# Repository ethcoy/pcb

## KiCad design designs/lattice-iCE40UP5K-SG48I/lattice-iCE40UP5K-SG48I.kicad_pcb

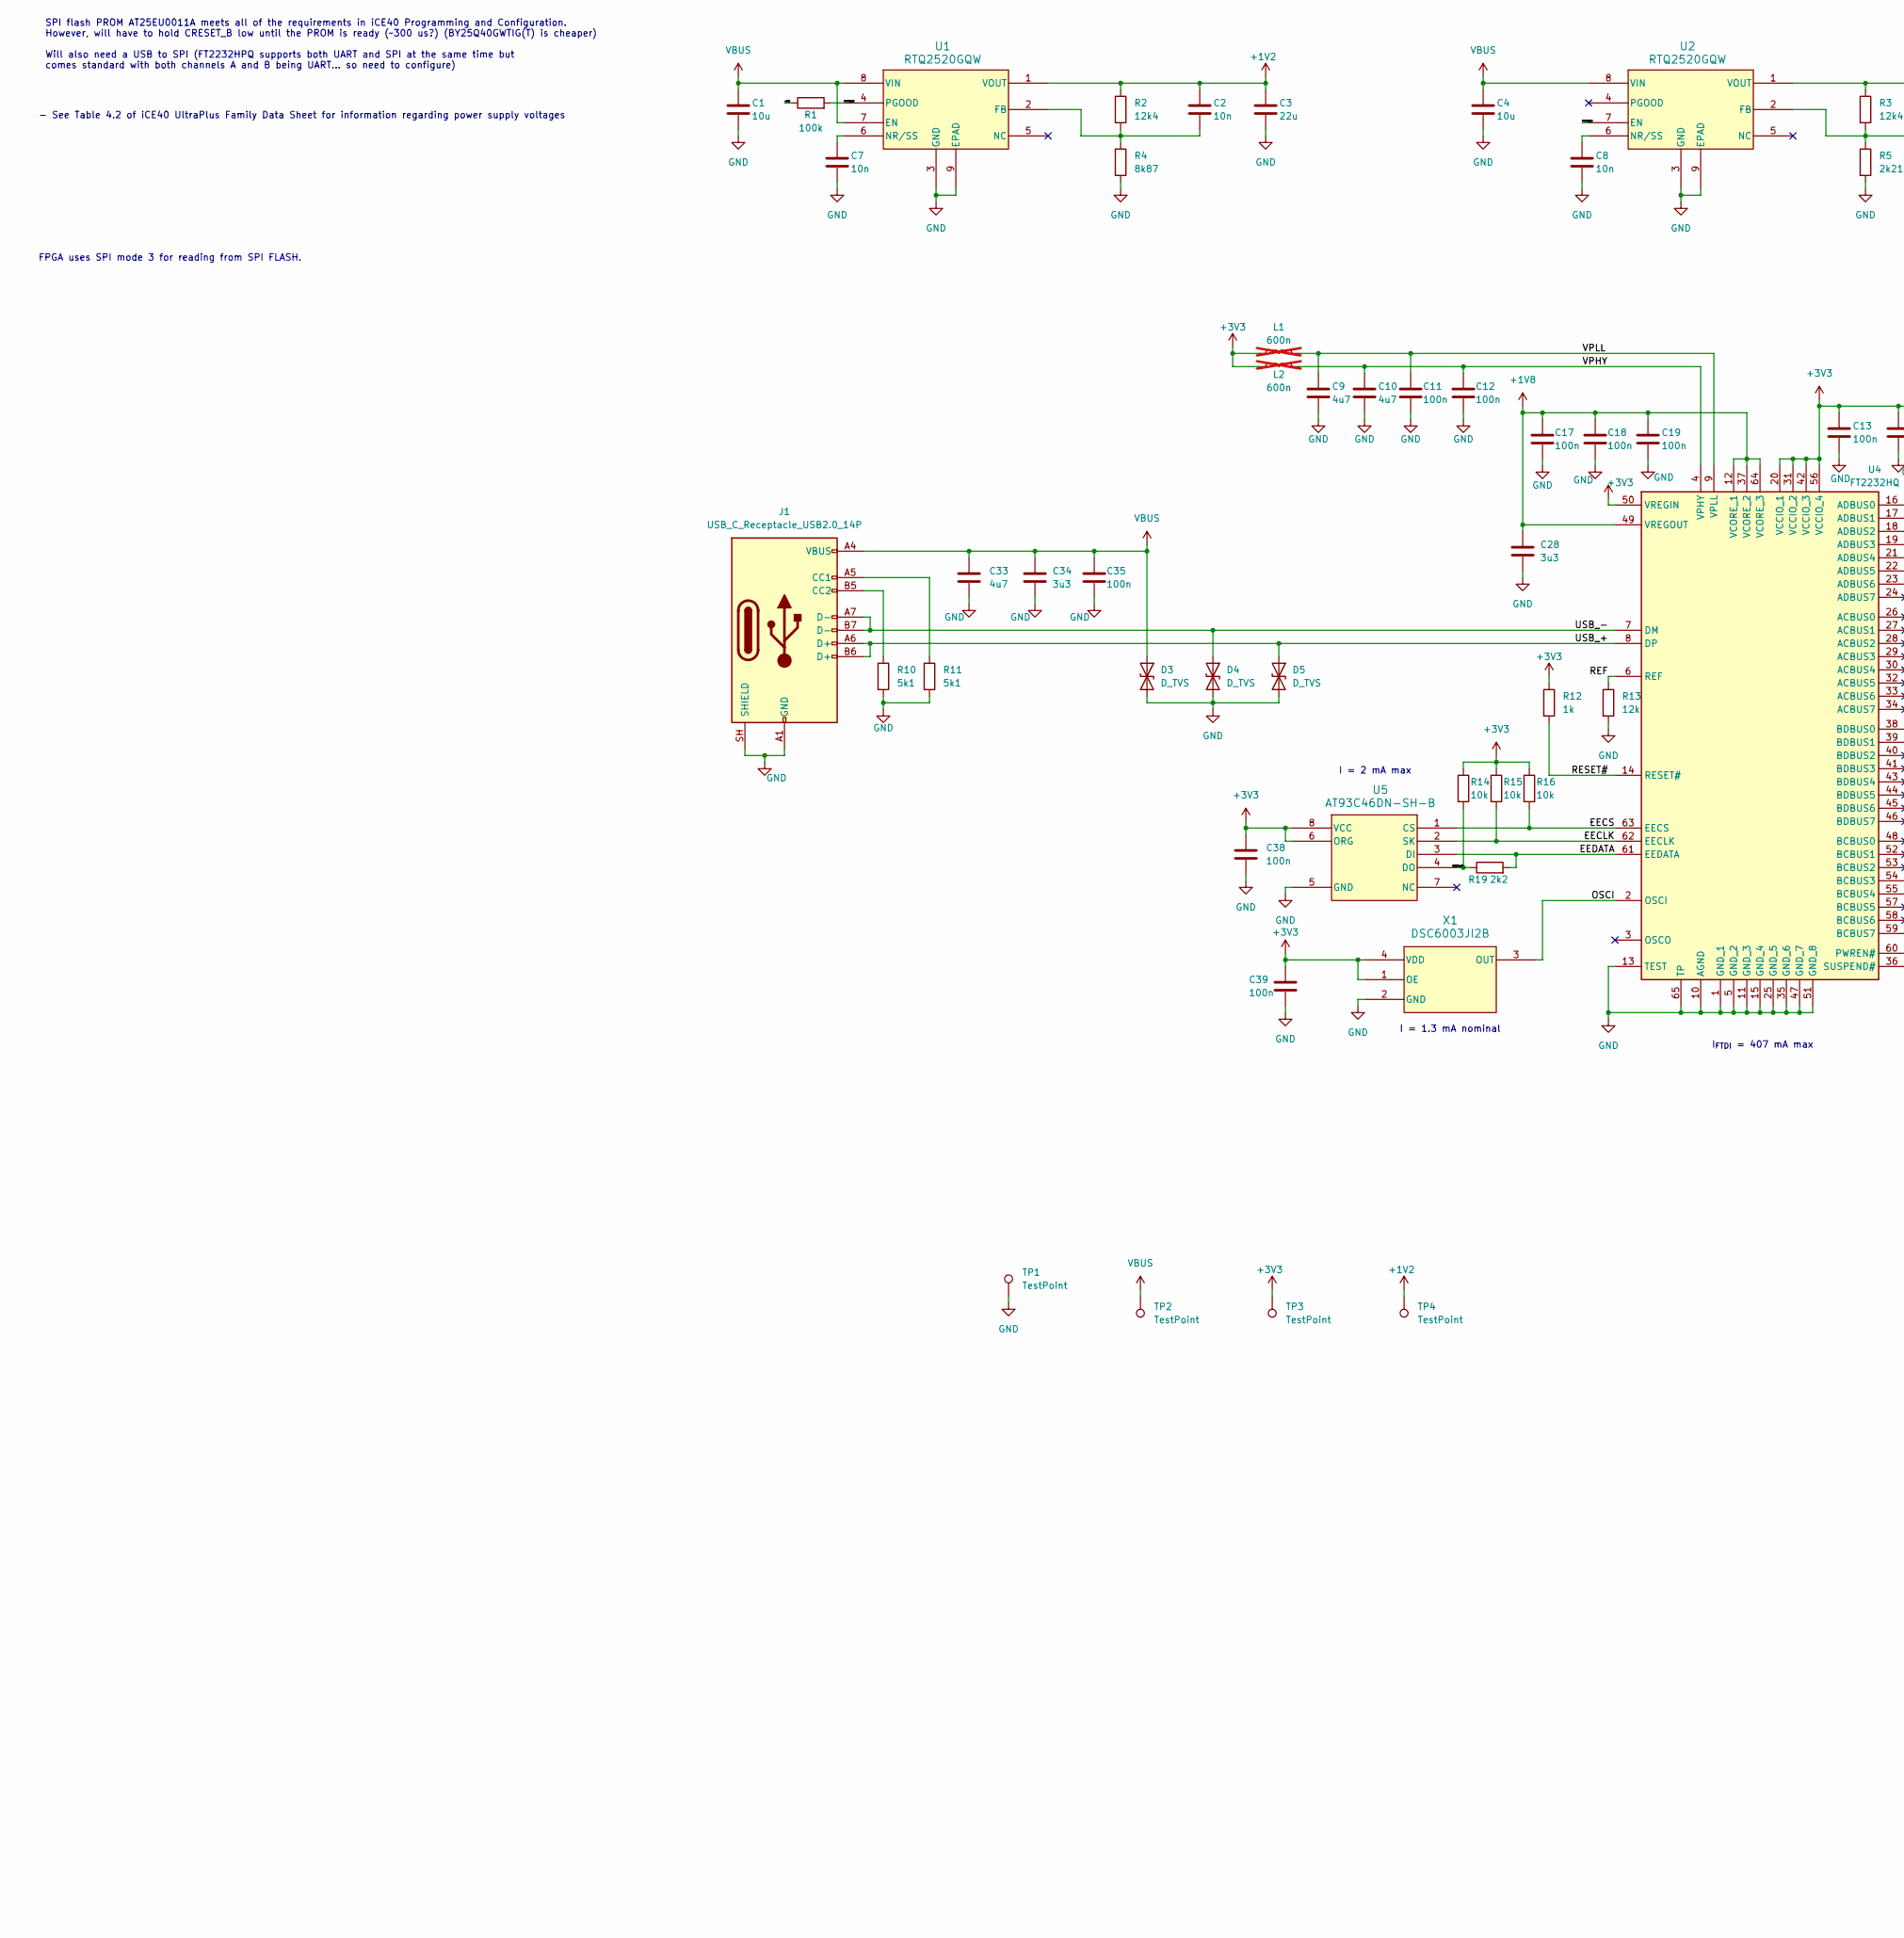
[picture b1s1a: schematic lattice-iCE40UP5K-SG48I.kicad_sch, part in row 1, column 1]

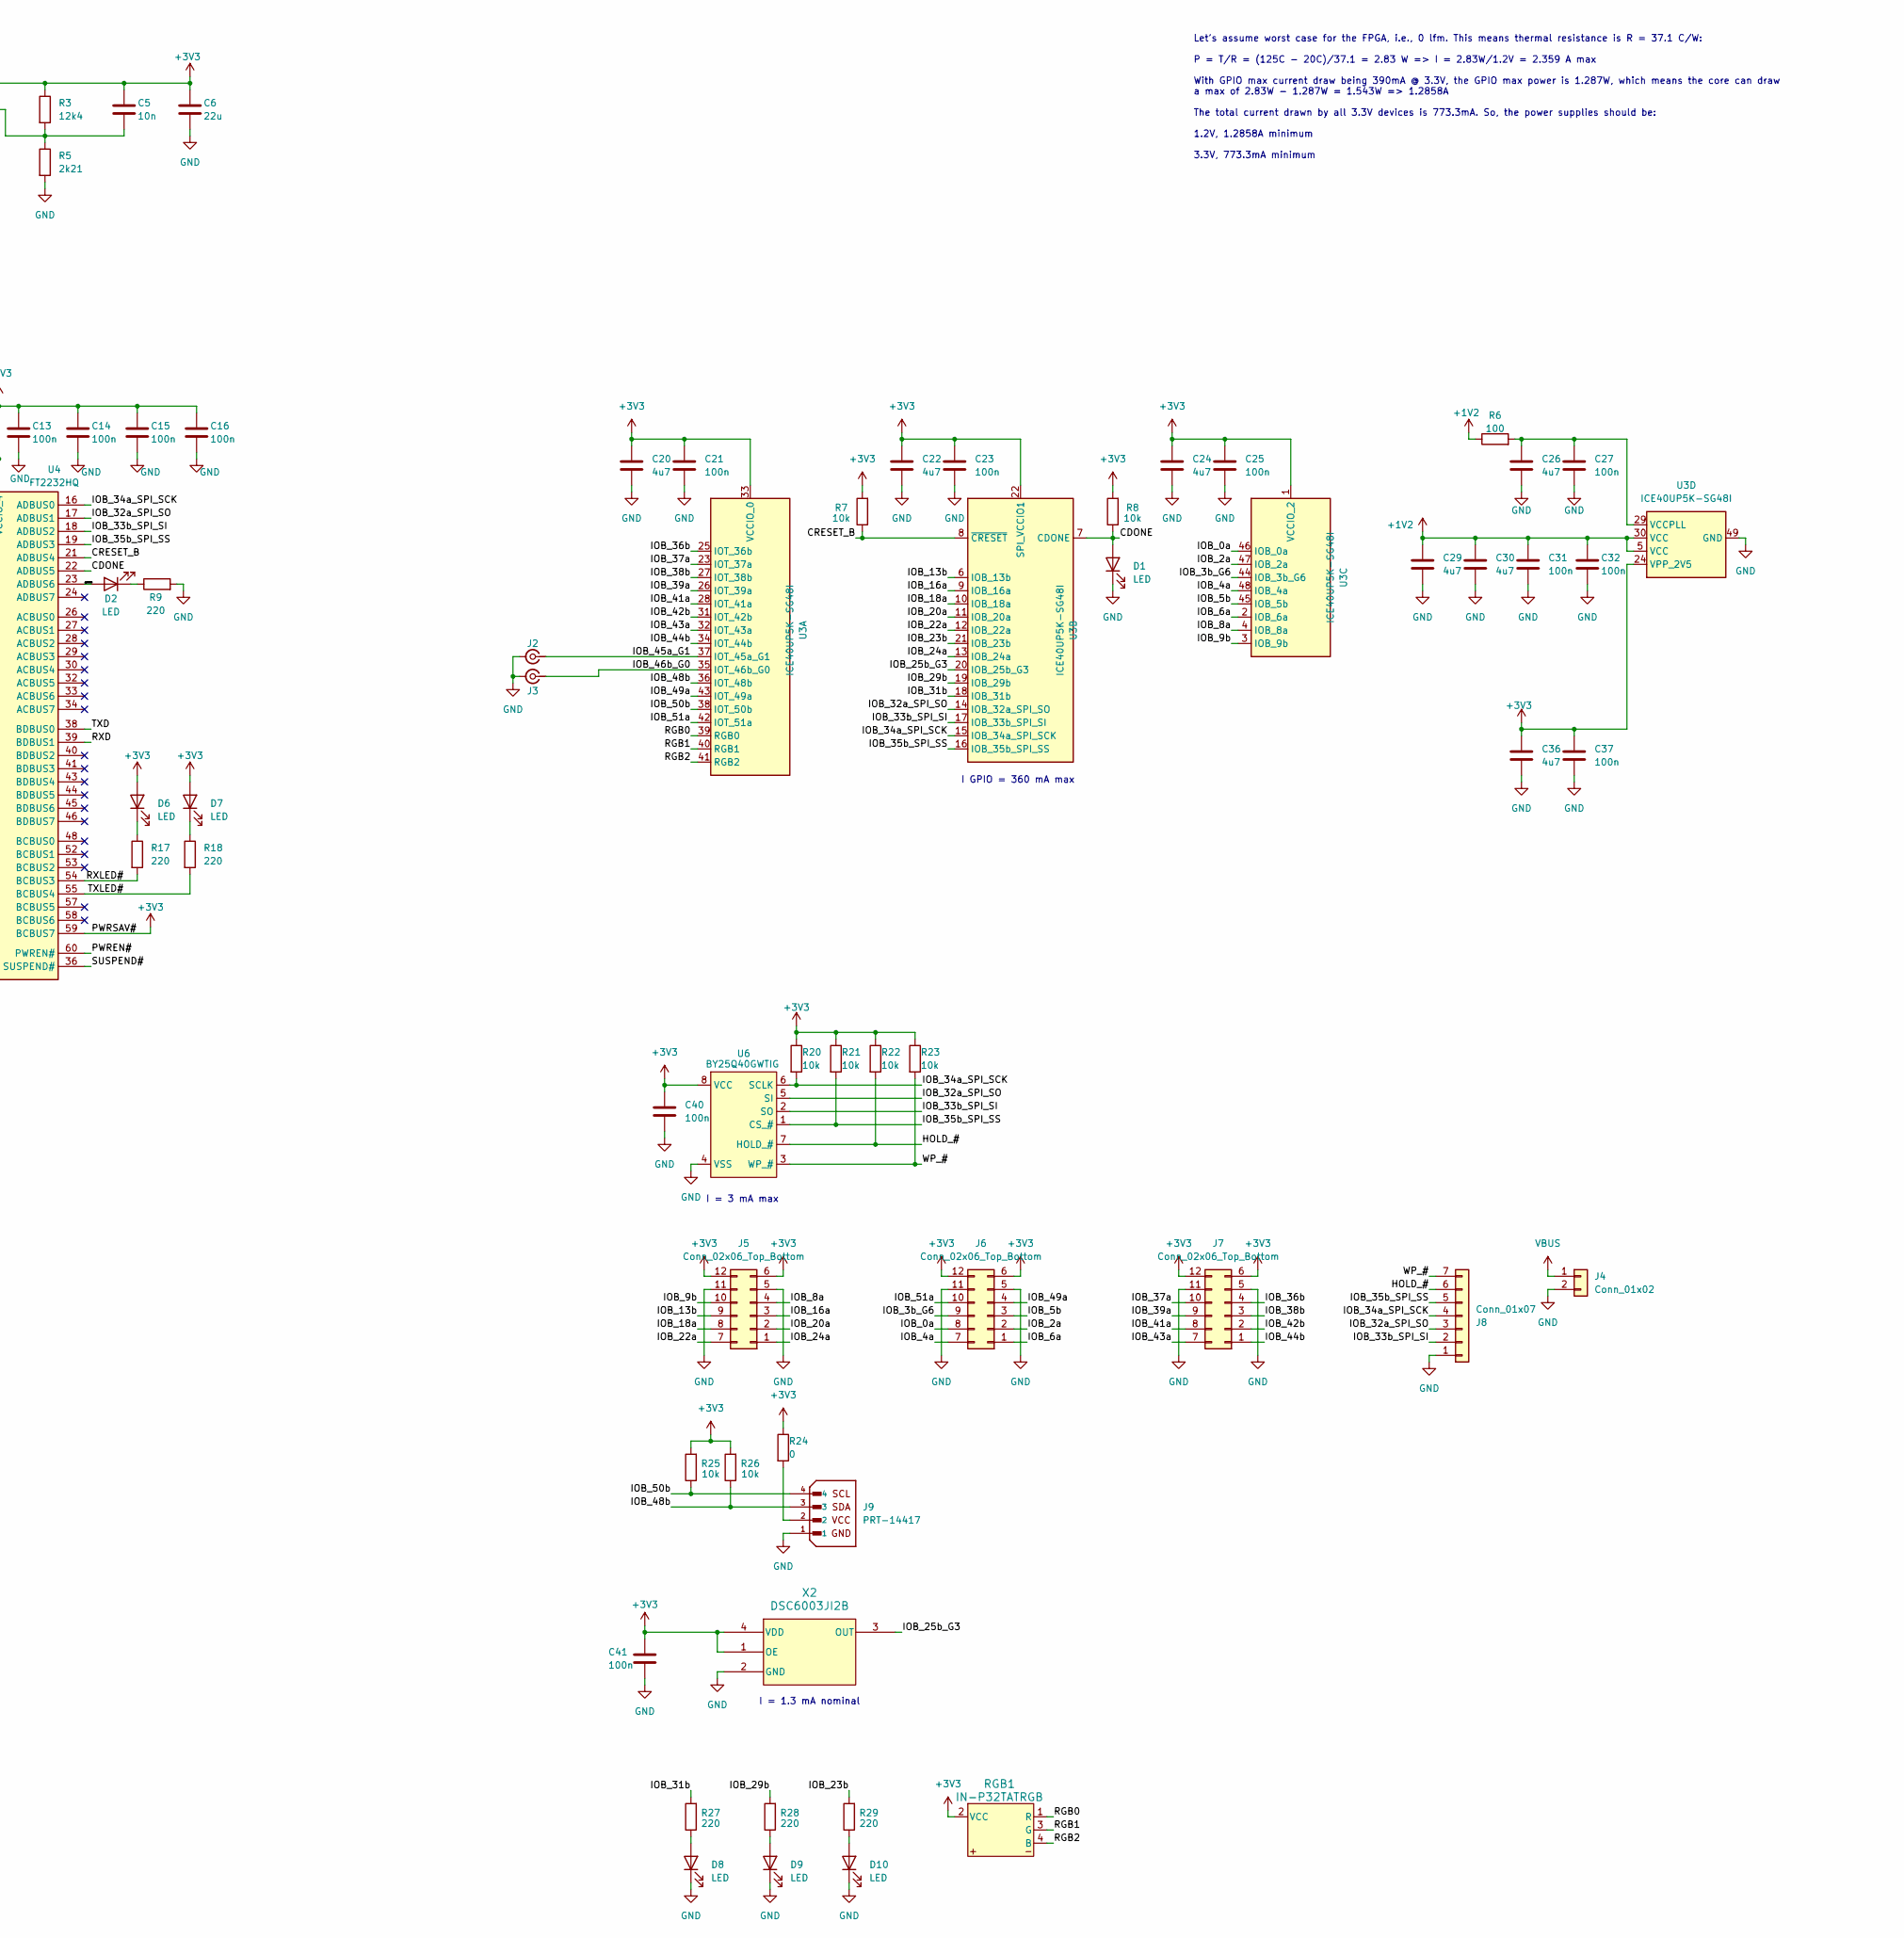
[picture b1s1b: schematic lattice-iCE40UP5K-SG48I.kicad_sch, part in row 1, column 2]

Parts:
C1, C4: 10u; C_0402_1005Metric
C2, C5, C7, C8: 10n; C_0402_1005Metric
C3, C6: 22u; C_0402_1005Metric
C9, C10, C20, C22, C24, C26, C29, C30, C33, C36: 4u7; C_0402_1005Metric
C11, C12, C13, C14, C15, C16, C17, C18, C19, C21, C23, C25, C27, C31, C32, C35, C37, C38, C39, C40, C41: 100n; C_0402_1005Metric
C28, C34: 3u3; C_0402_1005Metric
D1, D2, D6, D7, D8, D9, D10: LED; D_0402_1005Metric
D3, D4, D5: D_TVS; D_SOD-523
J1: USB_C_Receptacle_USB2.0_14P; USB_C_Receptacle_GCT_USB4110
J2: Conn_Coaxial_Small; U.FL_Molex_MCRF_73412-0110_Vertical
J3: U.FL_Molex_MCRF_73412-0110_Vertical
J4: Conn_01x02; PinHeader_1x02_P2.54mm_Vertical_SMD_Pin1Left
J5, J6, J7: Conn_02x06_Top_Bottom; SAMTEC-SMH-106-02-X-D
J8: Conn_01x07; PinHeader_1x07_P2.54mm_Vertical_SMD_Pin1Left
J9: PRT-14417; PARTREV NA
L1, L2: 600n; L_0402_1005Metric; not fitted
R1: 100k; R_0402_1005Metric
R2, R3: 12k4; R_0402_1005Metric
R4: 8k87; R_0402_1005Metric
R5: 2k21; R_0402_1005Metric
R6: 100; R_0402_1005Metric
R7, R8, R14, R15, R16, R20, R21, R22, R23, R25, R26: 10k; R_0402_1005Metric
R9, R17, R18, R27, R28, R29: 220; R_0402_1005Metric
R10, R11: 5k1; R_0402_1005Metric
R12: 1k; R_0402_1005Metric
R13: 12k; R_0402_1005Metric
R19: 2k2; R_0402_1005Metric
R24: 0; R_0402_1005Metric
RGB1: IN-P32TATRGB; 4-PLCC_3P2X2P8_INL
TP1, TP2, TP3, TP4: TestPoint; TestPoint_Pad_D1.0mm
U1, U2: RTQ2520GQW
U3: ICE40UP5K-SG48I; QFN50P700X700X100-49N-D
U4: FT2232HQ; Mouser Part Number 895-FT2232HQ
U5: AT93C46DN-SH-B
U6: BY25Q40GWTIG
X1, X2: DSC6003JI2B

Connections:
+1V2: C2.1, C3.1, C29.1, C30.1, C31.1, C32.1, R1.1, R2.1, R6.1, TP4.1 (1_1), U1.1 (VOUT), U3.5 (VCC), U3.30 (VCC)
+1V8: C17.1, C18.1, C19.1, C28.1, U4.12 (VCORE_1), U4.37 (VCORE_2), U4.49 (VREGOUT), U4.64 (VCORE_3)
+3V3: C5.1, C6.1, C13.1, C14.1, C15.1, C16.1, C20.1, C21.1, C22.1, C23.1, C24.1, C25.1, C36.1, C37.1, C38.1, C39.1, C40.1, C41.1, D6.2 (A), D7.2 (A), J5.6, J5.12, J6.6, J6.12, J7.6, J7.12, L1.1, L2.1, R3.1, R7.2, R8.2, R12.1, R14.1, R15.1, R16.1, R20.1, R21.1, R22.1, R23.1, R24.1, R25.2, R26.2, RGB1.2 (VCC), TP3.1 (1_1), U2.1 (VOUT), U3.1 (VCCIO_2), U3.22 (SPI_VCCIO1), U3.24 (VPP_2V5), U3.33 (VCCIO_0), U4.20 (VCCIO_1), U4.31 (VCCIO_2), U4.42 (VCCIO_3), U4.50 (VREGIN), U4.56 (VCCIO_4), U4.59 (BCBUS7), U5.6 (ORG), U5.8 (VCC), U6.8 (VCC), X1.1 (OE), X1.4 (VDD), X2.1 (OE), X2.4 (VDD)
/ADBUS6: D2.2 (A), U4.23 (ADBUS6)
/CDONE: D1.2 (A), R8.1, U3.7 (CDONE), U4.22 (ADBUS5)
/CRESET_B: R7.1, U3.8 (~CRESET), U4.21 (ADBUS4)
/EECLK: R15.2, U4.62 (EECLK), U5.2 (SK)
/EECS: R16.2, U4.63 (EECS), U5.1 (CS)
/EEDATA: R19.2, U4.61 (EEDATA), U5.3 (DI)
/EEDATA_PU: R14.2, R19.1, U5.4 (DO)
/HOLD_#: J8.6, R22.2, U6.7 (HOLD_#)
/IOB_0a: J6.8, U3.46 (IOB_0a)
/IOB_2a: J6.2, U3.47 (IOB_2a)
/IOB_3b_G6: J6.9, U3.44 (IOB_3b_G6)
/IOB_4a: J6.7, U3.48 (IOB_4a)
/IOB_5b: J6.3, U3.45 (IOB_5b)
/IOB_6a: J6.1, U3.2 (IOB_6a)
/IOB_8a: J5.4, U3.4 (IOB_8a)
/IOB_9b: J5.10, U3.3 (IOB_9b)
/IOB_13b: J5.9, U3.6 (IOB_13b)
/IOB_16a: J5.3, U3.9 (IOB_16a)
/IOB_18a: J5.8, U3.10 (IOB_18a)
/IOB_20a: J5.2, U3.11 (IOB_20a)
/IOB_22a: J5.7, U3.12 (IOB_22a)
/IOB_23b: R29.2, U3.21 (IOB_23b)
/IOB_24a: J5.1, U3.13 (IOB_24a)
/IOB_25b_G3: U3.20 (IOB_25b_G3), X2.3 (OUT)
/IOB_29b: R28.2, U3.19 (IOB_29b)
/IOB_31b: R27.2, U3.18 (IOB_31b)
/IOB_32a_SPI_SO: J8.3, U3.14 (IOB_32a_SPI_SO), U4.17 (ADBUS1), U6.5 (SI)
/IOB_33b_SPI_SI: J8.2, U3.17 (IOB_33b_SPI_SI), U4.18 (ADBUS2), U6.2 (SO)
/IOB_34a_SPI_SCK: J8.4, R20.2, U3.15 (IOB_34a_SPI_SCK), U4.16 (ADBUS0), U6.6 (SCLK)
/IOB_35b_SPI_SS: J8.5, R21.2, U3.16 (IOB_35b_SPI_SS), U4.19 (ADBUS3), U6.1 (CS_#)
/IOB_36b: J7.4, U3.25 (IOT_36b)
/IOB_37a: J7.10, U3.23 (IOT_37a)
/IOB_38b: J7.3, U3.27 (IOT_38b)
/IOB_39a: J7.9, U3.26 (IOT_39a)
/IOB_41a: J7.8, U3.28 (IOT_41a)
/IOB_42b: J7.2, U3.31 (IOT_42b)
/IOB_43a: J7.7, U3.32 (IOT_43a)
/IOB_44b: J7.1, U3.34 (IOT_44b)
/IOB_45a_G1: J2.1 (In), U3.37 (IOT_45a_G1)
/IOB_46b_G0: J3.1 (In), U3.35 (IOT_46b_G0)
/IOB_48b: J9.3, R26.1, U3.36 (IOT_48b)
/IOB_49a: J6.4, U3.43 (IOT_49a)
/IOB_50b: J9.4, R25.1, U3.38 (IOT_50b)
/IOB_51a: J6.10, U3.42 (IOT_51a)
/OSCI: U4.2 (OSCI), X1.3 (OUT)
/PGOOD1V2: R1.2, U1.4 (PGOOD), U2.7 (EN)
/PWREN#: U4.60 (PWREN#)
/REF: R13.1, U4.6 (REF)
/RESET#: R12.2, U4.14 (RESET#)
/RGB0: RGB1.1 (R), U3.39 (RGB0)
/RGB1: RGB1.3 (G), U3.40 (RGB1)
/RGB2: RGB1.4 (B), U3.41 (RGB2)
/RXD: U4.39 (BDBUS1)
/RXLED#: R17.2, U4.54 (BCBUS3)
/SUSPEND#: U4.36 (SUSPEND#)
/TXD: U4.38 (BDBUS0)
/TXLED#: R18.2, U4.55 (BCBUS4)
/USB_+: D5.1 (A1), J1.A6 (D+), J1.B6 (D+), U4.8 (DP)
/USB_-: D4.1 (A1), J1.A7 (D-), J1.B7 (D-), U4.7 (DM)
/VPHY: C10.1, C12.1, L2.2, U4.4 (VPHY)
/VPLL: C9.1, C11.1, L1.2, U4.9 (VPLL)
/WP_#: J8.7, R23.2, U6.3 (WP_#)
GND: C1.2, C3.2, C4.2, C6.2, C7.2, C8.2, C9.2, C10.2, C11.2, C12.2, C13.2, C14.2, C15.2, C16.2, C17.2, C18.2, C19.2, C20.2, C21.2, C22.2, C23.2, C24.2, C25.2, C26.2, C27.2, C28.2, C29.2, C30.2, C31.2, C32.2, C33.2, C34.2, C35.2, C36.2, C37.2, C38.2, C39.2, C40.2, C41.2, D1.1 (K), D3.2 (A2), D4.2 (A2), D5.2 (A2), D8.1 (K), D9.1 (K), D10.1 (K), J1.A1 (GND), J1.A12 (GND), J1.B1 (GND), J1.B12 (GND), J1.SH (SHIELD), J2.2 (Ext), J3.2 (Ext), J4.2, J5.5, J5.11, J6.5, J6.11, J7.5, J7.11, J8.1, J9.1, R4.2, R5.2, R9.2, R10.2, R11.2, R13.2, TP1.1 (1_1), U1.3 (GND), U1.9 (EPAD), U2.3 (GND), U2.9 (EPAD), U3.49 (GND), U4.1 (GND_1), U4.5 (GND_2), U4.10 (AGND), U4.11 (GND_3), U4.13 (TEST), U4.15 (GND_4), U4.25 (GND_5), U4.35 (GND_6), U4.47 (GND_7), U4.51 (GND_8), U4.65 (TP), U5.5 (GND), U6.4 (VSS), X1.2 (GND), X2.2 (GND)
unnamed: D2.1 (K), R9.1
unnamed: D6.1 (K), R17.1
unnamed: D7.1 (K), R18.1
unnamed: D8.2 (A), R27.1
unnamed: D9.2 (A), R28.1
unnamed: D10.2 (A), R29.1
unnamed: J1.A5 (CC1), R11.1
unnamed: J1.B5 (CC2), R10.1
unnamed: J9.2, R24.2
unnamed: C2.2, R2.2, R4.1, U1.2 (FB)
unnamed: C7.1, U1.6 (NR/SS)
unnamed: C5.2, R3.2, R5.1, U2.2 (FB)
unnamed: C8.1, U2.6 (NR/SS)
unnamed: C26.1, C27.1, R6.2, U3.29 (VCCPLL)
VBUS: C1.1, C4.1, C33.1, C34.1, C35.1, D3.1 (A1), J1.A4 (VBUS), J1.A9 (VBUS), J1.B4 (VBUS), J1.B9 (VBUS), J4.1, TP2.1 (1_1), U1.7 (EN), U1.8 (VIN), U2.8 (VIN)

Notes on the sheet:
I = 1.3 mA nominal
I_{FTDI} = 407 mA max
I GPIO = 360 mA max
I = 2 mA max
SPI flash PROM AT25EU0011A meets all of the requirements in iCE40 Programming and Configuration. However, will have to hold CRESET_B low until the PROM is ready (~300 us?) (BY25Q40GWTIG(T) is cheaper) Will also need a USB to SPI (FT2232HPQ supports both UART and SPI at the same time but comes stand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
FPGA uses SPI mode 3 for reading from SPI FLASH.
Let's assume worst case for the FPGA, i.e., 0 lfm. This means thermal resistance is R = 37.1 C/W: P = T/R = (125C - 20C)/37.1 = 2.83 W => I = 2.83W/1.2V = 2.359 A max With GPIO max current draw being 390mA @ 3.3V, the GPIO max power is 1.287W, which means the core can draw a max of 2.83W - 1.287W =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
I = 3 mA max
- See Table 4.2 of iCE40 UltraPlus Family Data Sheet for information regarding power supply voltages

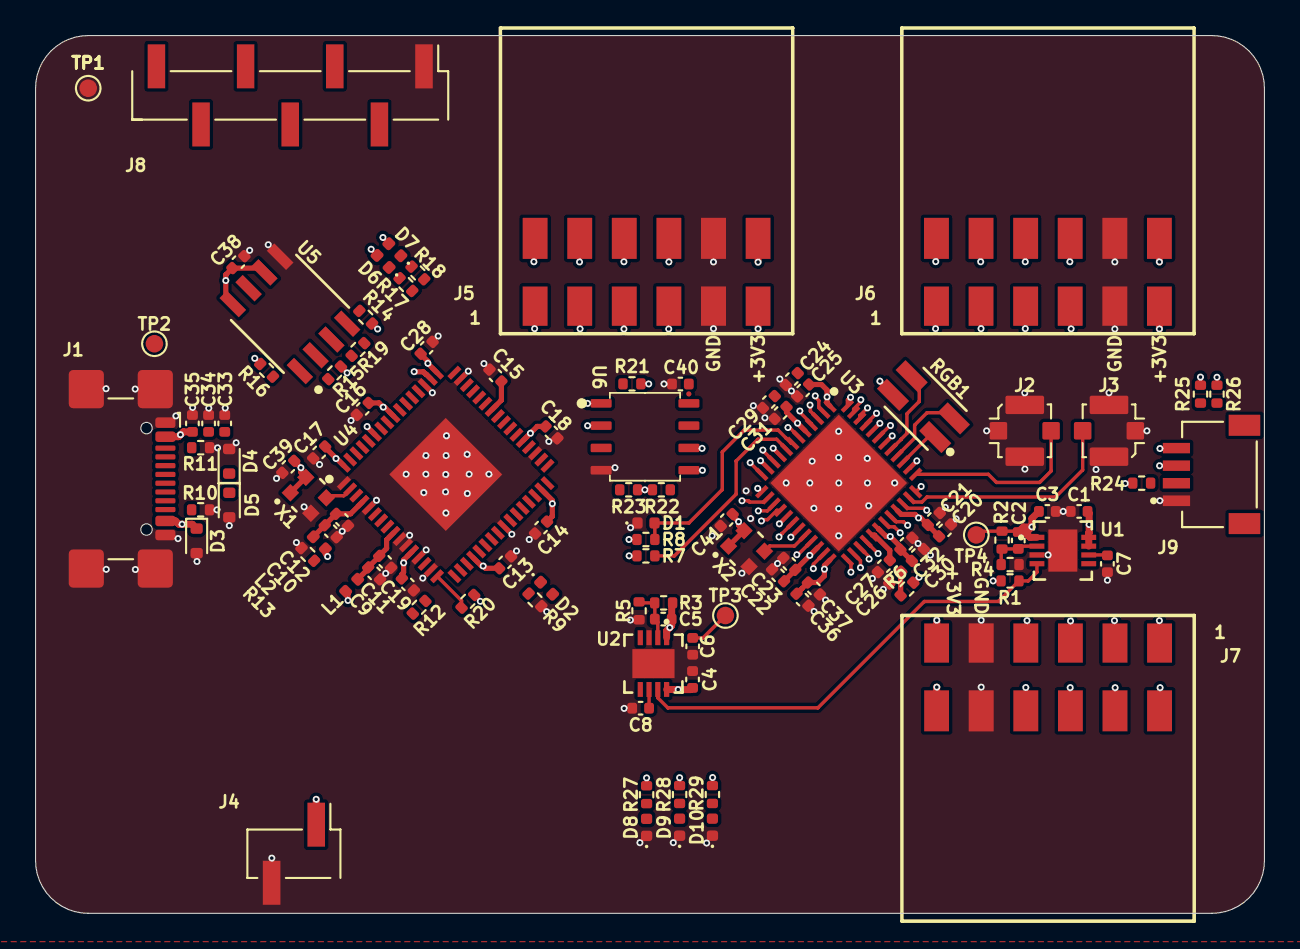
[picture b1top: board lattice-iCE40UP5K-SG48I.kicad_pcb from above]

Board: 6 copper layers, 70.0 x 50.0 mm, 104 parts (0 on the bottom side), 77 nets.

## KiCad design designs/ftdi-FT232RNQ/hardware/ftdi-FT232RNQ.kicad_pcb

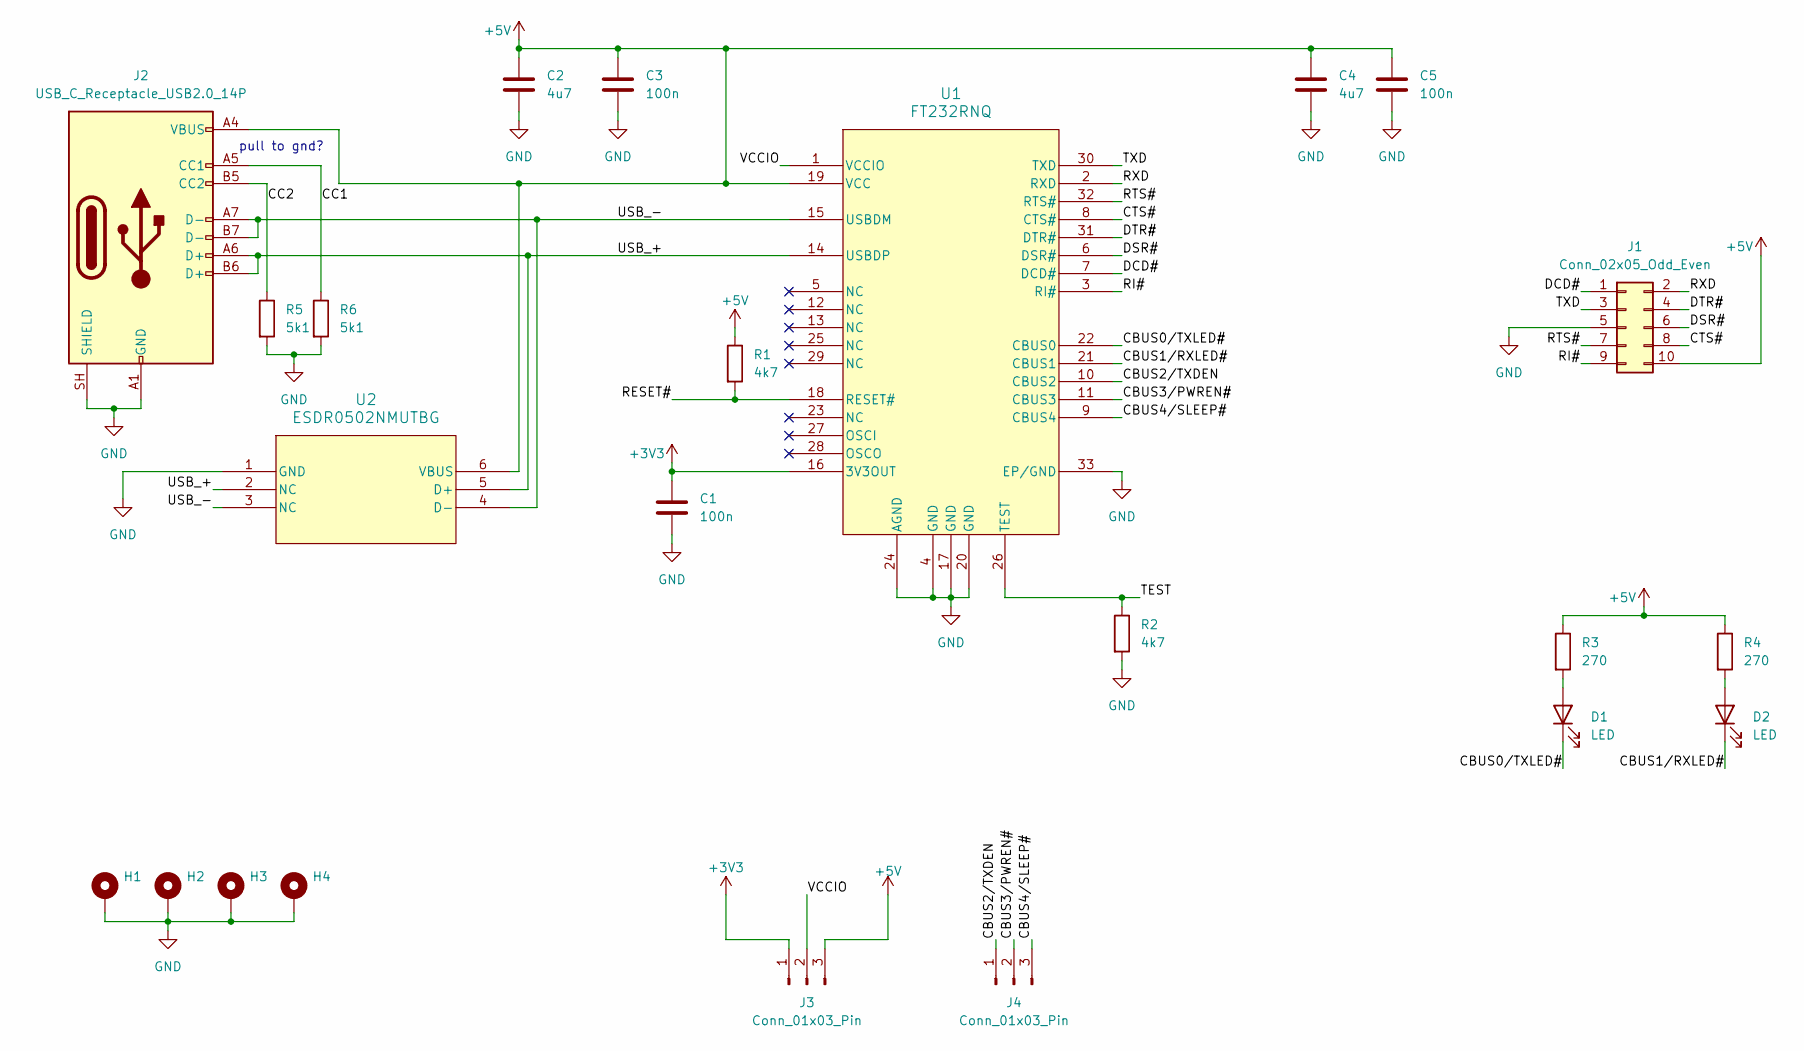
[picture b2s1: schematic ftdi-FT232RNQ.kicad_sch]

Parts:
C1, C3, C5: 100n; C_0402_1005Metric
C2, C4: 4u7; C_0402_1005Metric
D1, D2: LED; D_0402_1005Metric
H1, H2, H3, H4: MountingHole_Pad; MountingHole_3.2mm_M3_Pad_Via
J1: Conn_02x05_Odd_Even; IDC-Header_2x05_P2.54mm_Vertical_SMD
J2: USB_C_Receptacle_USB2.0_14P; USB_C_Receptacle_GCT_USB4110
J3, J4: Conn_01x03_Pin; PinHeader_1x03_P2.54mm_Vertical_SMD_Pin1Left
R1, R2: 4k7; R_0402_1005Metric
R3, R4: 270; R_0402_1005Metric
R5, R6: 5k1; R_0402_1005Metric
U1: FT232RNQ
U2: ESDR0502NMUTBG

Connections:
+3V3: C1.1, J3.1, U1.16 (3V3OUT)
+5V: C2.1, C3.1, C4.1, C5.1, J1.10, J2.A4 (VBUS), J2.A9 (VBUS), J2.B4 (VBUS), J2.B9 (VBUS), J3.3, R1.1, R3.1, R4.1, U1.19 (VCC), U2.6 (VBUS)
/CBUS0/TXLED#: D1.1 (K), U1.22 (CBUS0)
/CBUS1/RXLED#: D2.1 (K), U1.21 (CBUS1)
/CBUS2/TXDEN: J4.1, U1.10 (CBUS2)
/CBUS3/PWREN#: J4.2, U1.11 (CBUS3)
/CBUS4/SLEEP#: J4.3, U1.9 (CBUS4)
/CC1: J2.A5 (CC1), R6.1
/CC2: J2.B5 (CC2), R5.1
/CTS#: J1.8, U1.8 (CTS#)
/DCD#: J1.1, U1.7 (DCD#)
/DSR#: J1.6, U1.6 (DSR#)
/DTR#: J1.4, U1.31 (DTR#)
/RESET#: R1.2, U1.18 (RESET#)
/RI#: J1.9, U1.3 (RI#)
/RTS#: J1.7, U1.32 (RTS#)
/RXD: J1.2, U1.2 (RXD)
/TEST: R2.1, U1.26 (TEST)
/TXD: J1.3, U1.30 (TXD)
/USB_+: J2.A6 (D+), J2.B6 (D+), U1.14 (USBDP), U2.2 (NC), U2.5 (D+)
/USB_-: J2.A7 (D-), J2.B7 (D-), U1.15 (USBDM), U2.3 (NC), U2.4 (D-)
/VCCIO: J3.2, U1.1 (VCCIO)
GND: C1.2, C2.2, C3.2, C4.2, C5.2, H1.1 (1_1), H2.1 (1_1), H3.1 (1_1), H4.1 (1_1), J1.5, J2.A1 (GND), J2.A12 (GND), J2.B1 (GND), J2.B12 (GND), J2.SH (SHIELD), R2.2, R5.2, R6.2, U1.4 (GND), U1.17 (GND), U1.20 (GND), U1.24 (AGND), U1.33 (EP/GND), U2.1 (GND)
unnamed: D1.2 (A), R3.2
unnamed: D2.2 (A), R4.2

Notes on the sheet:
pull to gnd?

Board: 4 copper layers, 23 parts (0 on the bottom side), 25 nets, no tracks yet.

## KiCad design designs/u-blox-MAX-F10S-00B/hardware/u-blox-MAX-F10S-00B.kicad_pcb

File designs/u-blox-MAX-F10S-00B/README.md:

Breakout board for the u-blox MAX-F10S-00B

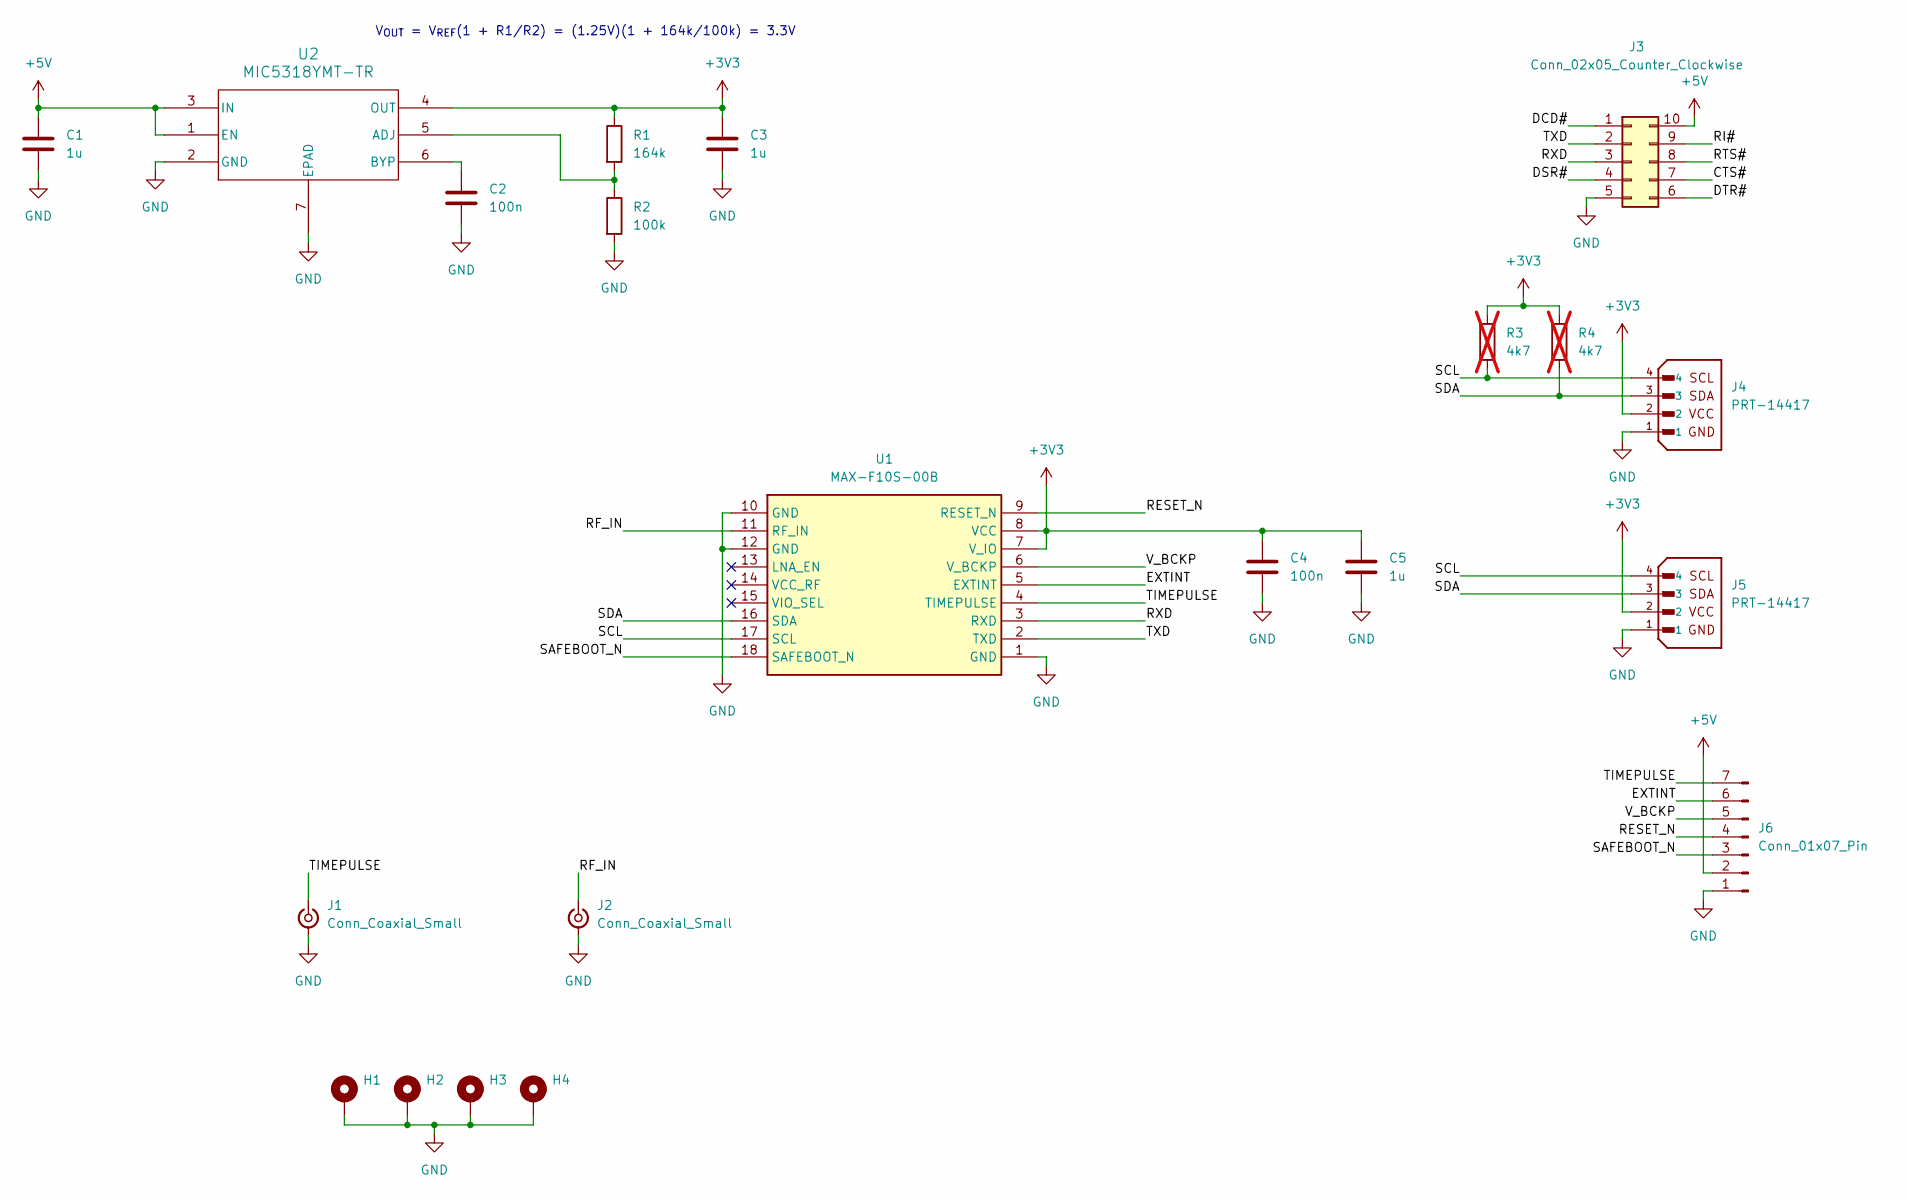
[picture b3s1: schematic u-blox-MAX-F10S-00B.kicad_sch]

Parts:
C1, C3, C5: 1u; C_0402_1005Metric
C2, C4: 100n; C_0402_1005Metric
H1, H2, H3, H4: MountingHole_Pad; MountingHole_3.2mm_M3_Pad_Via
J1, J2: Conn_Coaxial_Small; SMA_Amphenol_132289_EdgeMount
J3: Conn_02x05_Counter_Clockwise; PinHeader_2x05_P2.54mm_Vertical_SMD
J4, J5: PRT-14417; PARTREV NA
J6: Conn_01x07_Pin; PinHeader_1x07_P2.54mm_Vertical_SMD_Pin1Left
R1: 164k; R_0402_1005Metric
R2: 100k; R_0402_1005Metric
R3, R4: 4k7; R_0402_1005Metric; not fitted
U1: MAX-F10S-00B; MAXF10S00B; Mouser Part Number 377-MAX-F10S-00B
U2: MIC5318YMT-TR; TMLF-6_MT_MCH

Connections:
+3V3: C3.1, C4.1, C5.1, J4.2, J5.2, R1.1, R3.1, R4.1, U1.7 (V_IO), U1.8 (VCC), U2.4 (OUT)
+5V: C1.1, J3.10, J6.2, U2.1 (EN), U2.3 (IN)
/CTS#: J3.7
/DCD#: J3.1
/DSR#: J3.4
/DTR#: J3.6
/EXTINT: J6.6, U1.5 (EXTINT)
/RESET_N: J6.4, U1.9 (RESET_N)
/RF_IN: J2.1 (In), U1.11 (RF_IN)
/RI#: J3.9
/RTS#: J3.8
/RXD: J3.3, U1.3 (RXD)
/SAFEBOOT_N: J6.3, U1.18 (SAFEBOOT_N)
/SCL: J4.4, J5.4, R3.2, U1.17 (SCL)
/SDA: J4.3, J5.3, R4.2, U1.16 (SDA)
/TIMEPULSE: J1.1 (In), J6.7, U1.4 (TIMEPULSE)
/TXD: J3.2, U1.2 (TXD)
/V_BCKP: J6.5, U1.6 (V_BCKP)
GND: C1.2, C2.2, C3.2, C4.2, C5.2, H1.1 (1_1), H2.1 (1_1), H3.1 (1_1), H4.1 (1_1), J1.2 (Ext), J2.2 (Ext), J3.5, J4.1, J5.1, J6.1, R2.2, U1.1 (GND), U1.10 (GND), U1.12 (GND), U2.2 (GND), U2.7 (EPAD)
unnamed: R1.2, R2.1, U2.5 (ADJ)
unnamed: C2.1, U2.6 (BYP)

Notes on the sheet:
V_{OUT} = V_{REF}(1 + R1/R2) = (1.25V)(1 + 164k/100k) = 3.3V

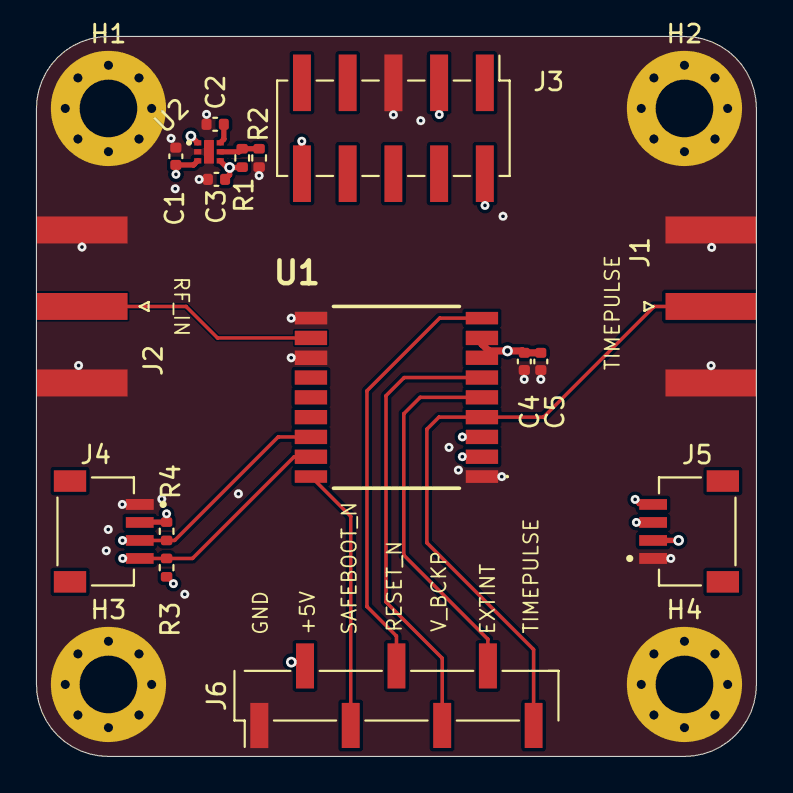
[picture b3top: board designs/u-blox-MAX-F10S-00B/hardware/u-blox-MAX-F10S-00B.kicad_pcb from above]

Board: 4 copper layers, 40.0 x 40.0 mm, 21 parts (0 on the bottom side), 15 nets.
